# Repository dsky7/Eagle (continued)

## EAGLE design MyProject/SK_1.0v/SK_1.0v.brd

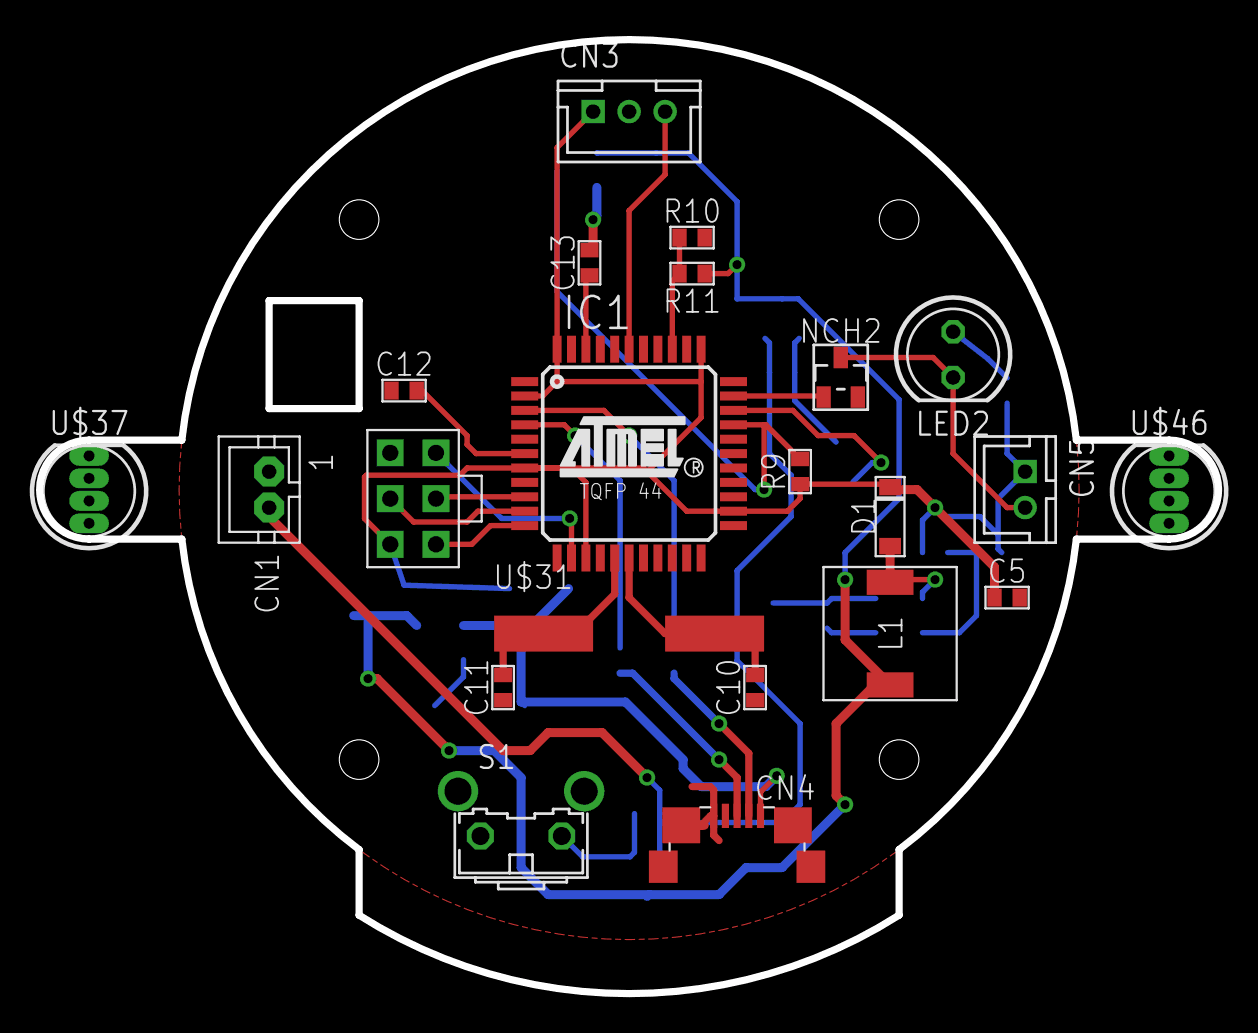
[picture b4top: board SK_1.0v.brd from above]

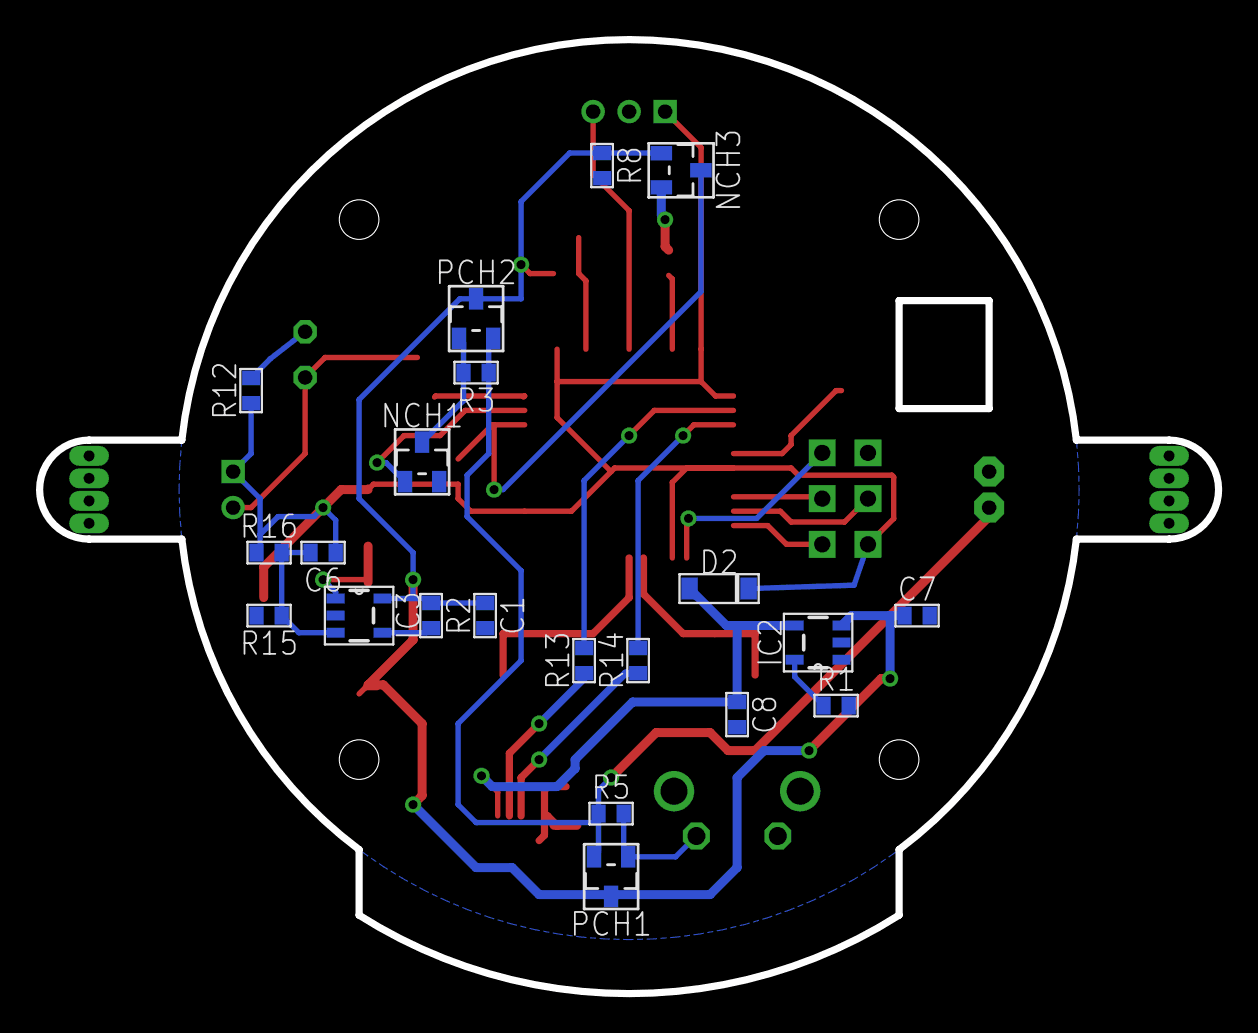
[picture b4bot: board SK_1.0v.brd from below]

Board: 2 copper layers, 65.5 x 53.0 mm, 43 parts (21 on the bottom side), 30 nets.

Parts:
C1, C5: 22uF; 1608
C6: 1nF; 1608
C7, C8: 4.7uF; 1608
C10, C11, C12, C13: 1608
CN1: JST-PH2
CN3: B3B-PH-K-S
CN4: MICRO-USB-SHIELD-ZX62R-B-5P; ZX62R-B-5P
CN5: B2B-PH-K-S
D1, D2: SOD-123; SOD_123
IC1: ATMEGA32U4-AU; TQFP44
IC2: MCP73831; SOT23-5L
IC3: LM2735; SOT23-5L
L1: 22uH; TOKO
LED2: 5MMLED; 5MM
NCH1, NCH2, NCH3: CHIP_FET; SOT23
PCH1, PCH2: CHIP_FET_P; SOT23
R1: 2K; 1608
R2, R15: 100K; 1608
R3, R5, R10, R11, R12, R13, R14: 1608
R8, R9: 10K; 1608
R16: 30K; 1608
S1: B3F-31XX
U$3: ICSP
U$31: CSM-7X-DU
U$37, U$46: NEO5MM

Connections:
+3.7V: C1.P$1, C7.P$1, IC2.3, IC3.5, L1.1, NCH3.1, PCH1.3, PCH2.3, R2.2, R8.2, R11.2
+5V: C5.P$1, C6.P$1, CN3.1, CN5.1, D1.C, D2.C, IC1.2, IC1.7, IC1.14, IC1.24, IC1.34, IC1.44, R9.2, R12.2, R16.2, U$3.2
+USB5V: C8.P$1, CN4.1, D2.A, IC2.4
A3: CN3.3, IC1.39
ADC0: IC1.36, R10.2, R11.1
D5: IC1.31, NCH1.1
D10: IC1.30, NCH3.3, R9.1
D13: IC1.32, NCH2.1
D+: CN4.3, R14.2
D-: CN4.2, R13.2
FB: C6.P$2, IC3.3, R15.2, R16.1
GND: C1.P$2, C5.P$2, C7.P$2, C8.P$2, C10.P$1, C11.P$1, C12.P$1, C13.P$2, CN1.1, CN3.2, CN4.5, CN4.M1, CN4.M2, CN4.M3, CN4.M4, IC1.5, IC1.15, IC1.23, IC1.35, IC1.43, IC2.2, IC3.2, NCH1.2, NCH2.2, NCH3.2, R1.1, R8.1, R10.1, R15.1, S1.1, U$3.6
MISO: IC1.11, U$3.1
MOSI: IC1.10, U$3.4
unnamed: CN5.2, LED2.K, NCH2.3
unnamed: IC2.5, R1.2
unnamed: IC3.4, R2.1
unnamed: D1.A, IC3.1, L1.2
unnamed: NCH1.3, PCH2.1, R3.1
unnamed: IC1.3, R13.1
unnamed: C13.P$1, IC1.42
unnamed: C10.P$2, IC1.17, U$31.2
unnamed: LED2.A, R12.1
unnamed: C11.P$2, IC1.16, U$31.1
unnamed: IC1.4, R14.1
unnamed: C12.P$2, IC1.6
RESET: IC1.13, U$3.5
SCLK: IC1.9, U$3.3
SWSIG: PCH1.1, R5.1, S1.2
V2: CN1.2, PCH1.2, PCH2.2, R3.2, R5.2

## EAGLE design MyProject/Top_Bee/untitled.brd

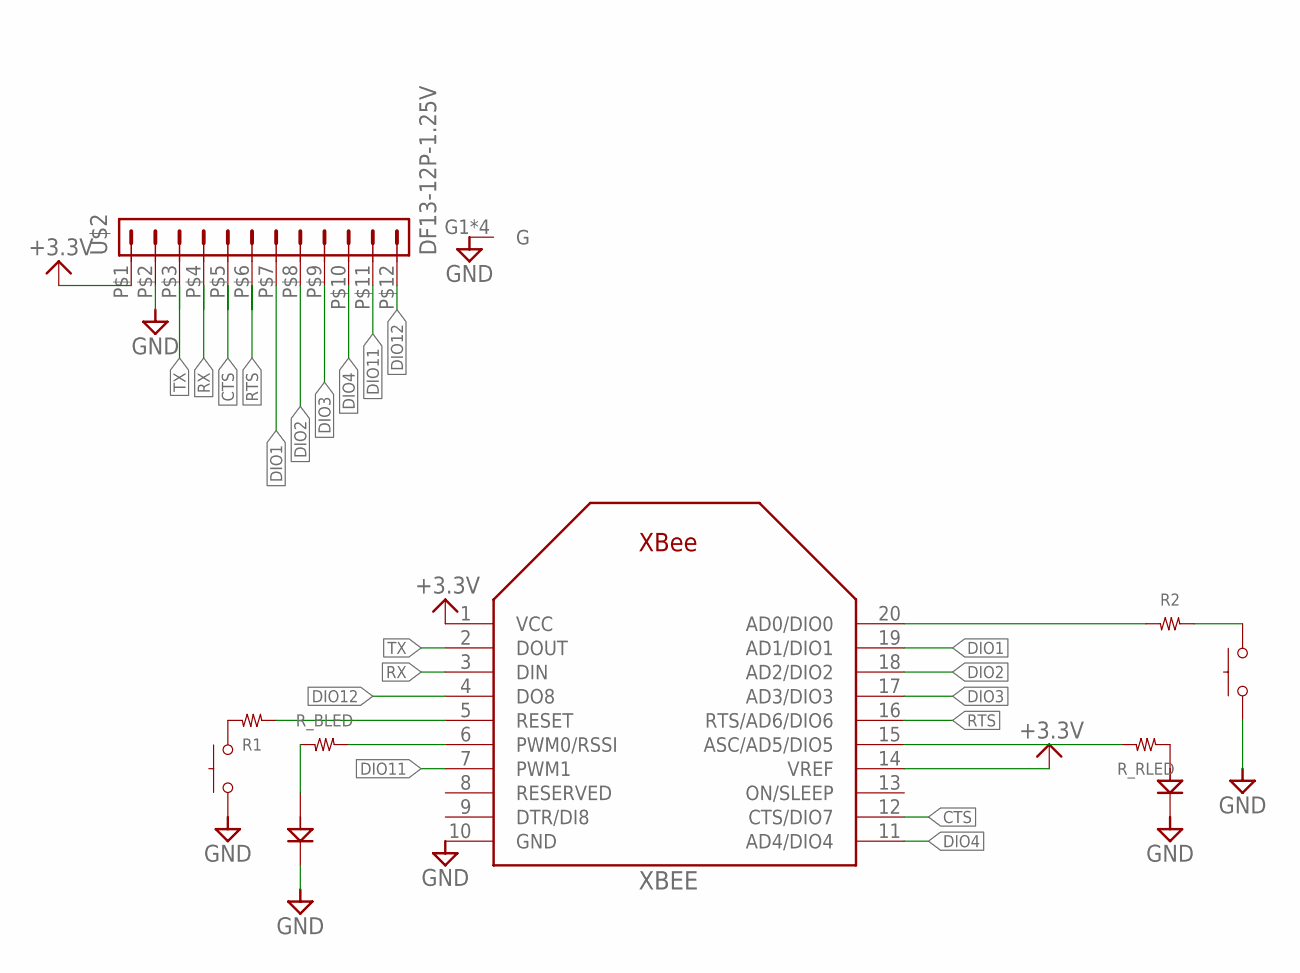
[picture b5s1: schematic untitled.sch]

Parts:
COMM: SKRPACE010; SKRP
LED_B: 1608
LED_R: 1608
R1, R2: RESISTOR__SMD; 1608
RESET: SKRPACE010; SKRP
R_BLED: RESISTOR__SMD; 1608
R_RLED: RESISTOR__SMD; 1608
U$2: DF13-12P-1.25V; DF13C-12P-1.25V
XBEE: XBEE

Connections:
+3.3V: U$2.P$1 (1), XBEE.1 (VCC), XBEE.14 (VREF)
CTS: U$2.P$5 (5), XBEE.12 (CTS/DIO7)
DIO1: U$2.P$7 (7), XBEE.19 (AD1/DIO1)
DIO2: U$2.P$8 (8), XBEE.18 (AD2/DIO2)
DIO3: U$2.P$9 (9), XBEE.17 (AD3/DIO3)
DIO4: U$2.P$10 (10), XBEE.11 (AD4/DIO4)
DIO11: U$2.P$11 (11), XBEE.7 (PWM1)
DIO12: U$2.P$12 (12), XBEE.4 (DO8)
GND: COMM.3, COMM.4, LED_B.2 (K), LED_R.2 (K), RESET.3, RESET.4, U$2.G1 (G), U$2.G2 (G), U$2.M$0 (G), U$2.M$1 (G), U$2.P$2 (2), XBEE.10 (GND)
unnamed: LED_R.1 (A), R_RLED.1
unnamed: R2.1, XBEE.20 (AD0/DIO0)
unnamed: R1.1, XBEE.5 (RESET)
unnamed: R1.2, RESET.1, RESET.2
unnamed: COMM.1, COMM.2, R2.2
unnamed: R_BLED.2, XBEE.6 (PWM0/RSSI)
unnamed: R_RLED.2, XBEE.15 (ASC/AD5/DIO5)
unnamed: LED_B.1 (A), R_BLED.1
RTS: U$2.P$6 (6), XBEE.16 (RTS/AD6/DIO6)
RX: U$2.P$4 (4), XBEE.3 (DIN)
TX: U$2.P$3 (3), XBEE.2 (DOUT)

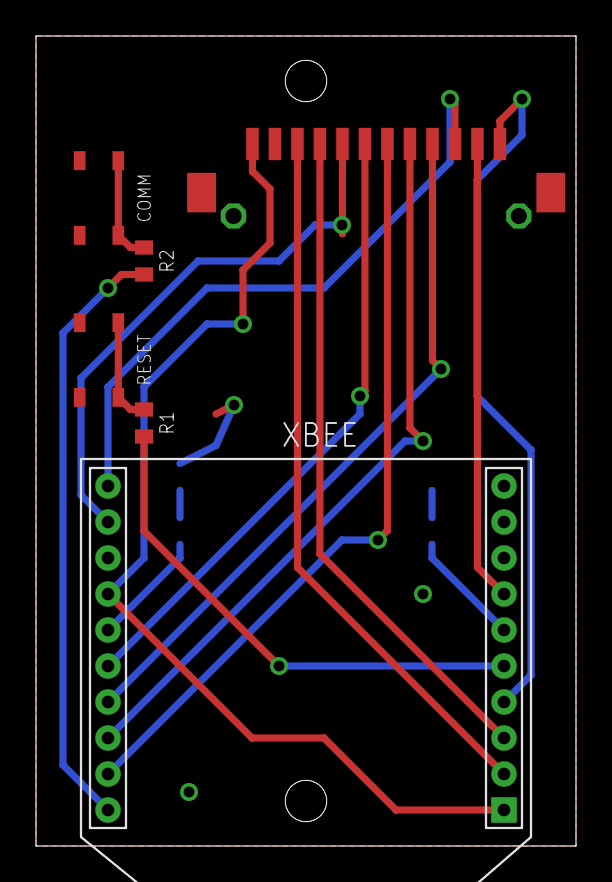
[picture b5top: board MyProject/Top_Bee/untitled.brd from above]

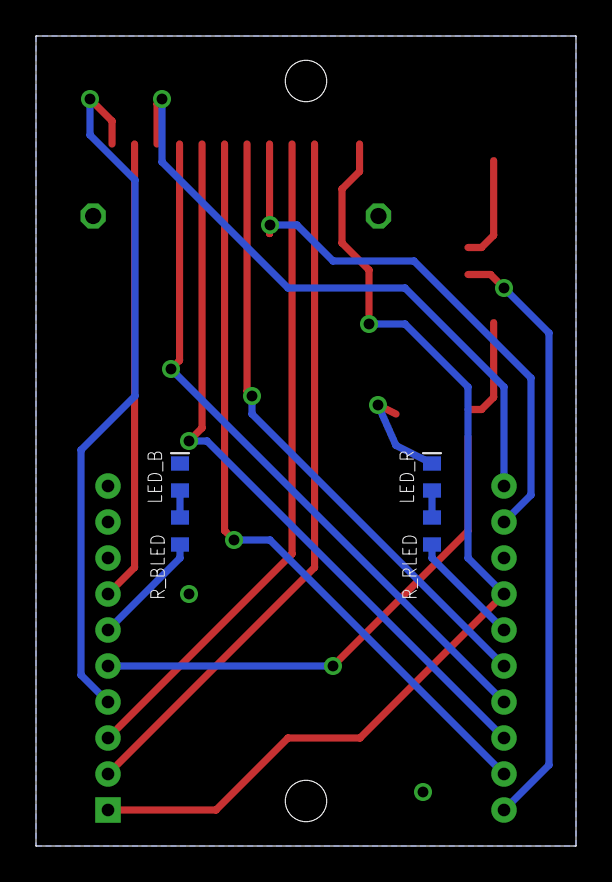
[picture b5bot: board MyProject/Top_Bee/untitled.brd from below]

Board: 2 copper layers, 30.0 x 45.0 mm, 10 parts (4 on the bottom side), 20 nets.
